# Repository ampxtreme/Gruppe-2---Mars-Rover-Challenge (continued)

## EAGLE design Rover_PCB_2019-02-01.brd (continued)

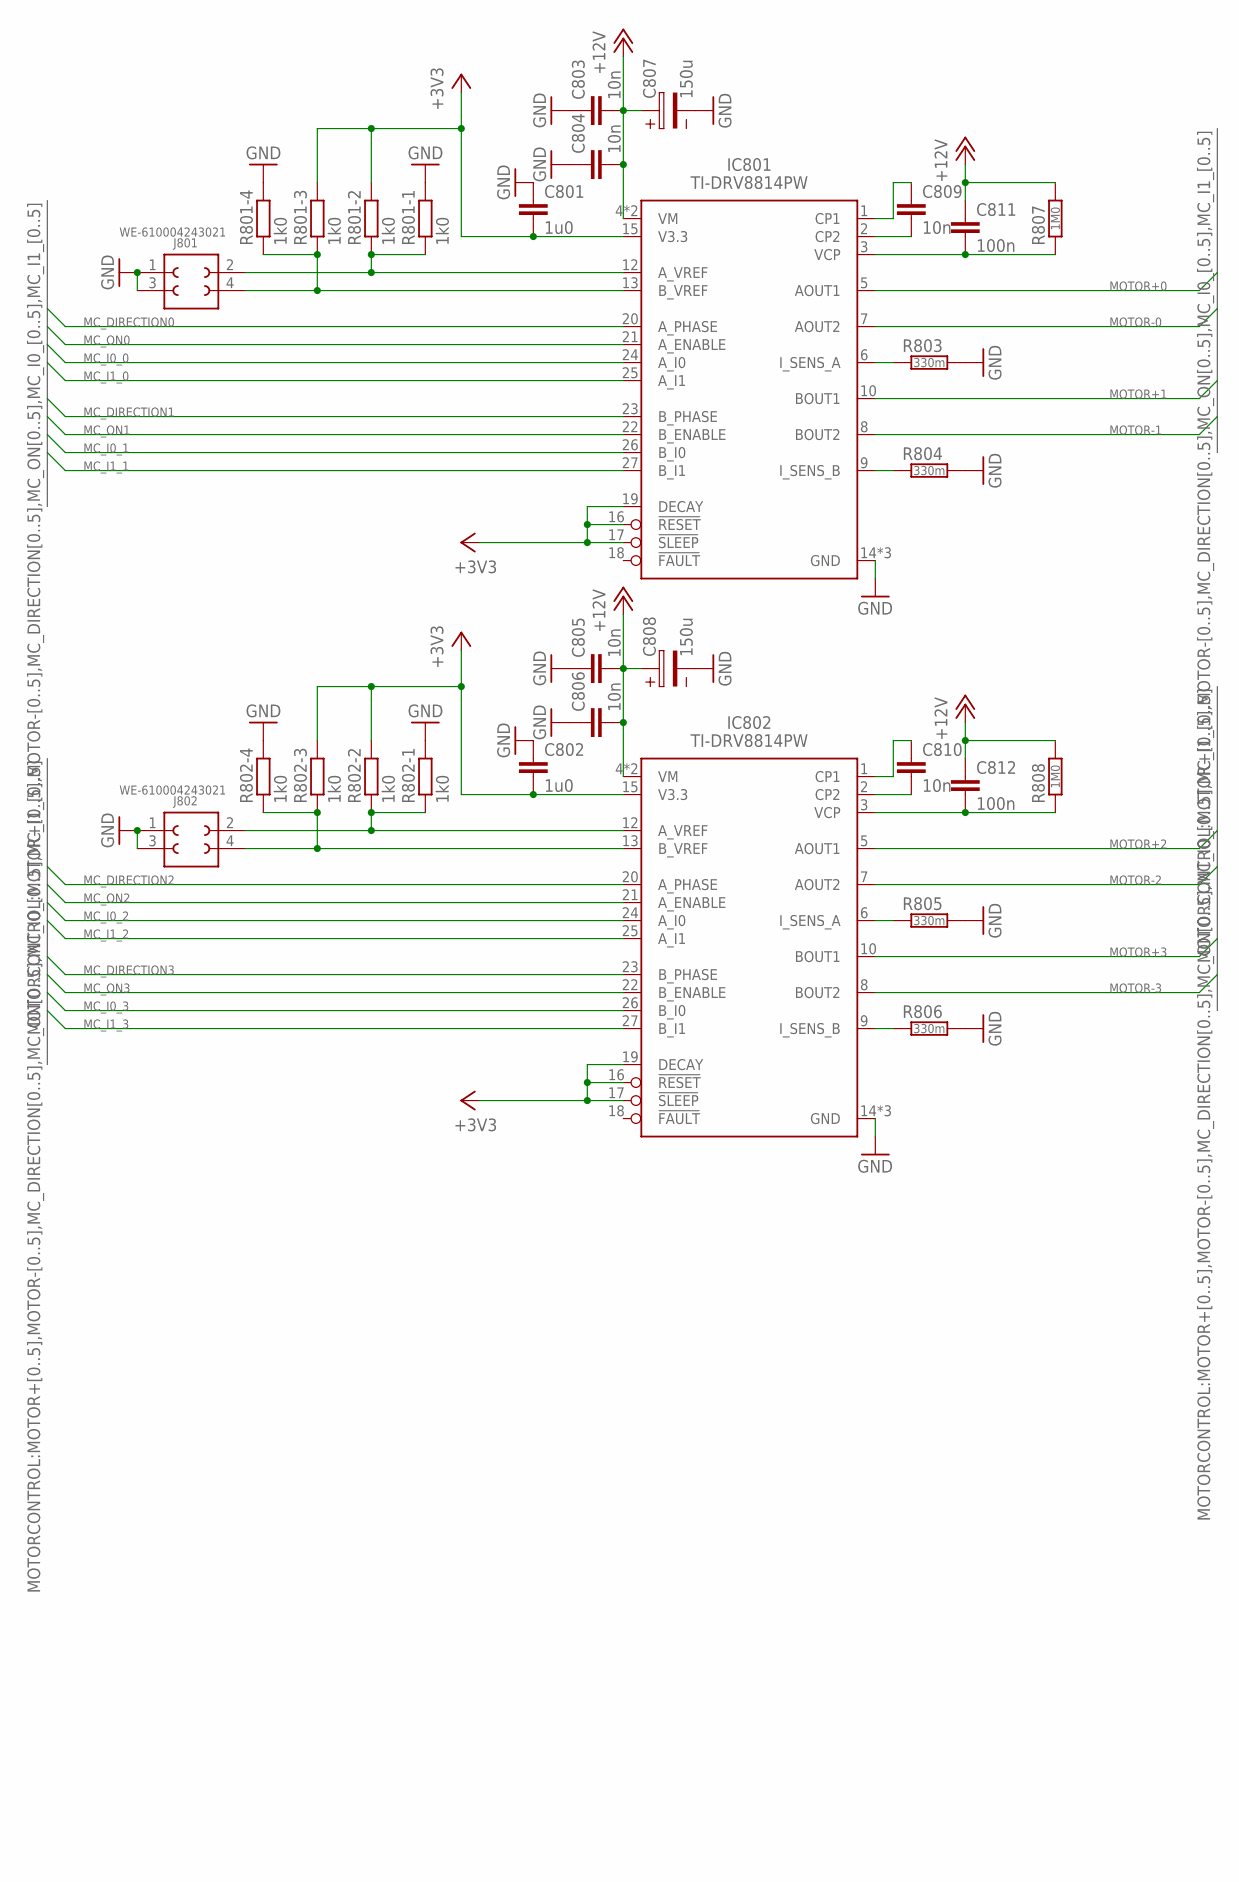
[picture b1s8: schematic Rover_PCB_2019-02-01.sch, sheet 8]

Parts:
C801, C802: 1u0; CAPC2012X95N
C803, C804, C805, C806, C809, C810: 10n; CAPC2012X95N
C807, C808: 150u; 4.2X1.9X2.8(BXCXA)
C811, C812: 100n; CAPC2012X95N
IC801, IC802: TI-DRV8814PW; SOP29P65_970X640X120L60X24T500X270N
J801, J802: WE-610004243021; 610X04243021
R801, R802: 1k0; CAPCAF80P160X320X70-8L
R803, R804, R805, R806: 330m; RESC160X320X65L50L
R807, R808: 1M0; RESC2012X50N

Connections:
+3V3: C801.2, C802.2, IC801.15 (V3.3), IC801.16 (!RESET), IC801.17 (!SLEEP), IC801.19 (DECAY), IC802.15 (V3.3), IC802.16 (!RESET), IC802.17 (!SLEEP), IC802.19 (DECAY), R801.6 (2), R801.7 (2), R802.6 (2), R802.7 (2); also elsewhere on the board
+12V: C803.2, C804.2, C805.2, C806.2, C807.1, C808.1, C811.1, C812.1, IC801.4 (VM), IC801.11 (VM), IC802.4 (VM), IC802.11 (VM), R807.2, R808.2; also elsewhere on the board
GND: C801.1, C802.1, C803.1, C804.1, C805.1, C806.1, C807.2, C808.2, IC801.14 (GND), IC801.28 (GND), IC801.29 (GND), IC802.14 (GND), IC802.28 (GND), IC802.29 (GND), J801.1, J801.3 (2), J802.1, J802.3 (2), R801.5 (2), R801.8 (2), R802.5 (2), R802.8 (2), R803.2, R804.2, R805.2, R806.2; also elsewhere on the board
MC_DIRECTION0: IC801.20 (A_PHASE); also elsewhere on the board
MC_DIRECTION1: IC801.23 (B_PHASE); also elsewhere on the board
MC_DIRECTION2: IC802.20 (A_PHASE); also elsewhere on the board
MC_DIRECTION3: IC802.23 (B_PHASE); also elsewhere on the board
MC_I0_0: IC801.24 (A_I0); also elsewhere on the board
MC_I0_1: IC801.26 (B_I0); also elsewhere on the board
MC_I0_2: IC802.24 (A_I0); also elsewhere on the board
MC_I0_3: IC802.26 (B_I0); also elsewhere on the board
MC_I1_0: IC801.25 (A_I1); also elsewhere on the board
MC_I1_1: IC801.27 (B_I1); also elsewhere on the board
MC_I1_2: IC802.25 (A_I1); also elsewhere on the board
MC_I1_3: IC802.27 (B_I1); also elsewhere on the board
MC_ON0: IC801.21 (A_ENABLE); also elsewhere on the board
MC_ON1: IC801.22 (B_ENABLE); also elsewhere on the board
MC_ON2: IC802.21 (A_ENABLE); also elsewhere on the board
MC_ON3: IC802.22 (B_ENABLE); also elsewhere on the board
MOTOR+0: IC801.5 (AOUT1); also elsewhere on the board
MOTOR+1: IC801.10 (BOUT1); also elsewhere on the board
MOTOR+2: IC802.5 (AOUT1); also elsewhere on the board
MOTOR+3: IC802.10 (BOUT1); also elsewhere on the board
MOTOR-0: IC801.7 (AOUT2); also elsewhere on the board
MOTOR-1: IC801.8 (BOUT2); also elsewhere on the board
MOTOR-2: IC802.7 (AOUT2); also elsewhere on the board
MOTOR-3: IC802.8 (BOUT2); also elsewhere on the board
unnamed: C811.2, IC801.3 (VCP), R807.1
unnamed: C809.2, IC801.2 (CP2)
unnamed: C809.1, IC801.1 (CP1)
unnamed: IC801.6 (I_SENS_A), R803.1
unnamed: IC801.9 (I_SENS_B), R804.1
unnamed: IC801.13 (B_VREF), J801.4 (3), R801.3 (1), R801.4 (1)
unnamed: IC801.12 (A_VREF), J801.2 (4), R801.1, R801.2 (1)
unnamed: C812.2, IC802.3 (VCP), R808.1
unnamed: C810.2, IC802.2 (CP2)
unnamed: C810.1, IC802.1 (CP1)
unnamed: IC802.6 (I_SENS_A), R805.1
unnamed: IC802.9 (I_SENS_B), R806.1
unnamed: IC802.13 (B_VREF), J802.4 (3), R802.3 (1), R802.4 (1)
unnamed: IC802.12 (A_VREF), J802.2 (4), R802.1, R802.2 (1)

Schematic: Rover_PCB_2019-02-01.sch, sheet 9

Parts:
C901: 1u0; CAPC2012X95N
C902, C903, C905: 10n; CAPC2012X95N
C904: 150u; 4.2X1.9X2.8(BXCXA)
C906: 100n; CAPC2012X95N
IC901: TI-DRV8814PW; SOP29P65_970X640X120L60X24T500X270N
J901: WE-610004243021; 610X04243021
R901: 1k0; CAPCAF80P160X320X70-8L
R902, R903: 330m; RESC160X320X65L50L
R904: 1M0; RESC2012X50N

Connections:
+3V3: C901.2, IC901.15 (V3.3), IC901.16 (!RESET), IC901.17 (!SLEEP), IC901.19 (DECAY), R901.6 (2), R901.7 (2); also elsewhere on the board
+12V: C902.2, C903.2, C904.1, C906.1, IC901.4 (VM), IC901.11 (VM), R904.2; also elsewhere on the board
GND: C901.1, C902.1, C903.1, C904.2, IC901.14 (GND), IC901.28 (GND), IC901.29 (GND), J901.1, J901.3 (2), R901.5 (2), R901.8 (2), R902.2, R903.2; also elsewhere on the board
MC_DIRECTION4: IC901.20 (A_PHASE); also elsewhere on the board
MC_DIRECTION5: IC901.23 (B_PHASE); also elsewhere on the board
MC_I0_4: IC901.24 (A_I0); also elsewhere on the board
MC_I0_5: IC901.26 (B_I0); also elsewhere on the board
MC_I1_4: IC901.25 (A_I1); also elsewhere on the board
MC_I1_5: IC901.27 (B_I1); also elsewhere on the board
MC_ON4: IC901.21 (A_ENABLE); also elsewhere on the board
MC_ON5: IC901.22 (B_ENABLE); also elsewhere on the board
MOTOR+4: IC901.5 (AOUT1); also elsewhere on the board
MOTOR+5: IC901.10 (BOUT1); also elsewhere on the board
MOTOR-4: IC901.7 (AOUT2); also elsewhere on the board
MOTOR-5: IC901.8 (BOUT2); also elsewhere on the board
unnamed: C906.2, IC901.3 (VCP), R904.1
unnamed: C905.2, IC901.2 (CP2)
unnamed: C905.1, IC901.1 (CP1)
unnamed: IC901.6 (I_SENS_A), R902.1
unnamed: IC901.9 (I_SENS_B), R903.1
unnamed: IC901.13 (B_VREF), J901.4 (3), R901.3 (1), R901.4 (1)
unnamed: IC901.12 (A_VREF), J901.2 (4), R901.1, R901.2 (1)

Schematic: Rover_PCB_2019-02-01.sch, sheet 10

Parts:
R7, R8: 1k0; CAPCAF80P160X320X70-8L
S1: WE-428521520816; 428521520816
S2, S3: WE-430172085816; 4301X20438X6

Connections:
+3V3: R8.5 (2), R8.6 (2), R8.7 (2), R8.8 (2), S1.C1, S1.C2; also elsewhere on the board
GND: R7.1, R7.2 (1), R7.3 (1), R7.4 (1), S2.3 (2), S2.4, S3.3 (2), S3.4; also elsewhere on the board
GPIO21: R8.3 (1), S2.1; also elsewhere on the board
GPIO22: R8.4 (1), S3.1; also elsewhere on the board
GPIO25: R7.7 (2), S1.8; also elsewhere on the board
GPIO27: R7.8 (2), S1.1; also elsewhere on the board
GPIO28: R7.6 (2), S1.2; also elsewhere on the board
GPIO29: R7.5 (2), S1.4; also elsewhere on the board

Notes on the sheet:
rot
schwarz
Drehwahlschalter

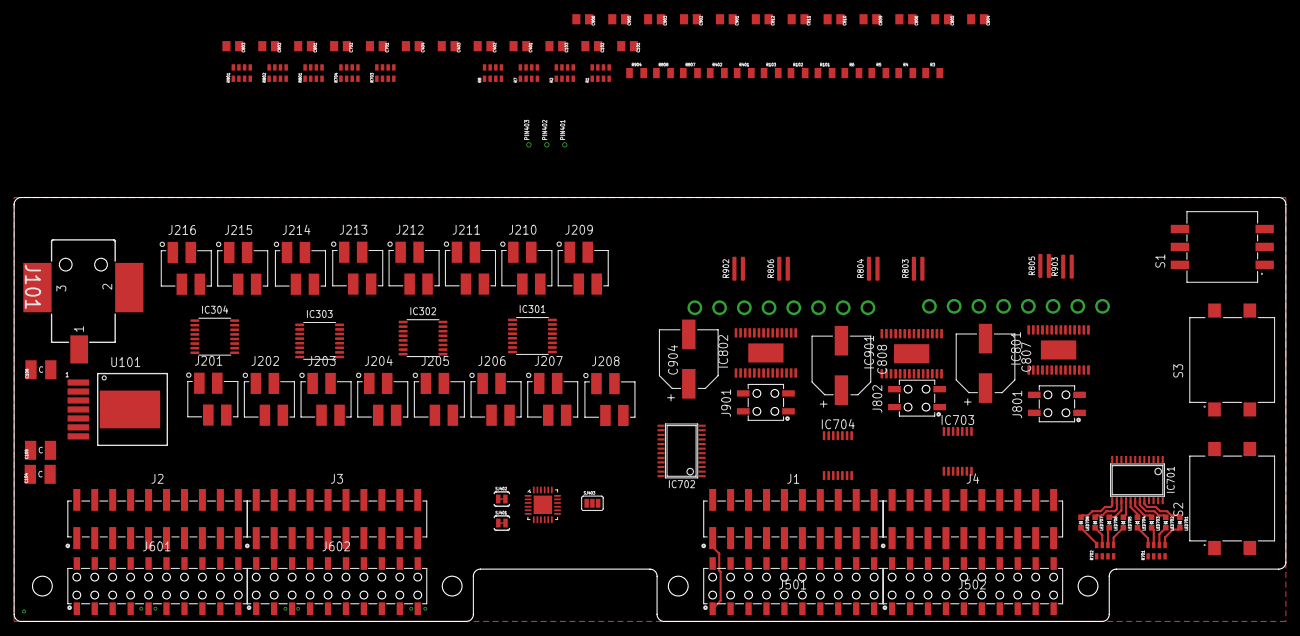
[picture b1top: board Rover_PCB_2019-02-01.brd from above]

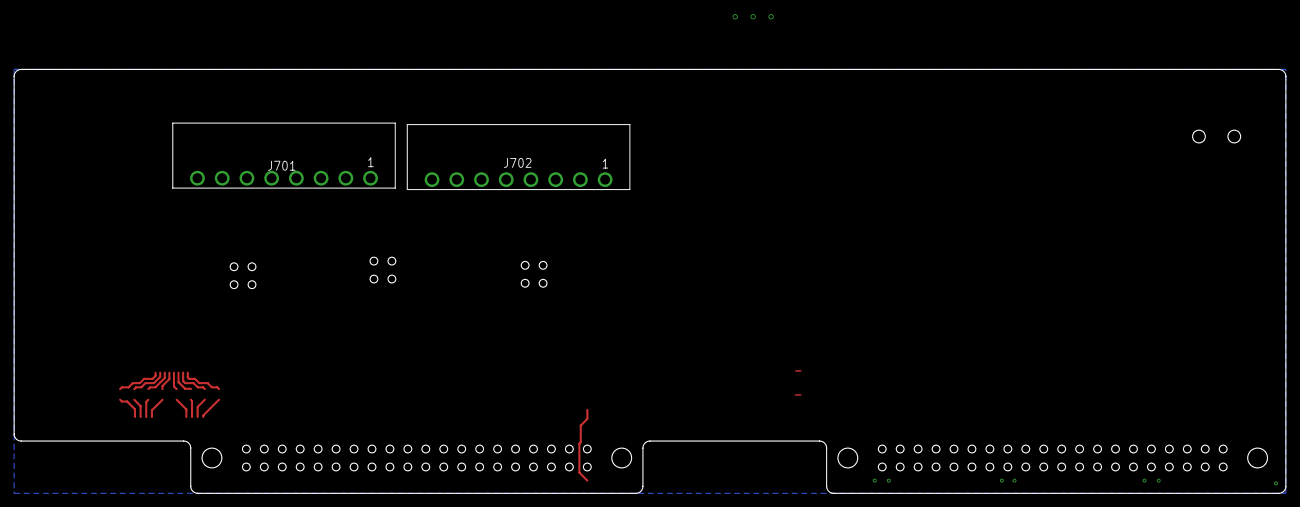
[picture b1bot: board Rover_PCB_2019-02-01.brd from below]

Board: 4 copper layers, 180.0 x 60.0 mm, 119 parts (2 on the bottom side), 190 nets.

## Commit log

2019-01-19 Create material.txt
    Materialsammlung
2019-01-22 Update 1
    Sortiert und erweitert. Ggf. fehlen noch Teile. Li
2019-01-22 Format
2019-01-22 Add files via upload
    Das ist der Deckel der Elektronik-Schachtel
2019-01-23 Rename Software/bgr_hsv_converter.py to Software/Objekterkennung/bgr_hsv_converter.py
2019-01-23 Rename Software/colorDetection.py to Software/Objekterkennung/colorDetection.py
2019-01-23 Rename Software/objectTracking.py to Software/Objekterkennung/objectTracking.py
2019-01-26 Create sghesgse
2019-01-29 Ablage
    asf
2019-02-05 Create ModulTests
2019-02-05 Rename _tmpl.py to linehold
2019-02-05 Rename linehold to linehold.py
2019-03-13 Create ...
2019-03-14 Create Rover
2019-03-30 Create LEDs Data
2019-04-07 git commit via console
